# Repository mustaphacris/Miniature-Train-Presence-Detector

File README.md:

# Description du détecteur de présence de train miniature

Le schéma électronique présenté permet de détecter la présence d’un train miniature sur une portion de voie alimentée en courant continu. Le principe repose sur la mesure du courant consommé par la locomotive ou par une résistance de détection placée sur les essieux du train. Lorsque le train est présent, un faible courant circule dans la voie, ce qui permet au circuit de le détecter et de générer un signal exploitable (par exemple pour commander un signal lumineux, une automatisation ou un système d’arrêt).

Le montage est composé de plusieurs blocs fonctionnels successifs :

## 1. Convertisseur courant/tension (U1A – LM358)

La présence du train provoque le passage d’un petit courant dans la voie. Ce courant circule à travers une résistance de shunt (R1), ce qui produit une tension proportionnelle.
L’amplificateur opérationnel U1A convertit cette variation de courant en une tension mesurable et l’amplifie.
→ Il transforme la présence de courant en un signal électrique exploitable.

## 2. Filtre passe–bande autour de 10 kHz (L1, C5, C6)

Pour éviter les fausses détections (bruits électriques, variations lentes), le signal passe dans un filtre passe-bande centré sur 10 kHz.
Ce filtre ne laisse passer que les variations rapides voulues, ce qui améliore la précision de détection.

## 3. Amplificateur non-inverseur (U1B – LM358)

Le signal filtré est ensuite amplifié à un niveau suffisant.
→ Cela garantit que le signal soit suffisamment fort pour être traité dans l’étape suivante.

## 4. Détecteur de crête (D2, R9, C9)

Ce circuit rectifie le signal et conserve sa valeur maximale dans le condensateur C9.
→ Le signal alternatif devient une tension continue, représentative de la présence du train.

## 5. Comparateur (U3 – LM393)

Le comparateur compare cette tension détectée à une tension de référence fixée par un potentiomètre.

Si la tension dépasse le seuil → présence du train détectée

Si elle est en dessous → aucun train sur la voie

La sortie du comparateur peut ensuite activer une LED, un relais ou envoyer un signal vers un système de commande.

##  6. Alimentation

Le montage fonctionne avec +5V et -5V.
Le -5V est généré automatiquement par un convertisseur DC-DC à pompe de charge (MAX1044).
→ Cela permet l’utilisation correcte des amplificateurs opérationnels.

# Description du routage de la carte électronique

Le routage de la carte électronique a été réalisé sur deux couches de cuivre : la couche F.Cu (face avant) et la couche B.Cu (face arrière). Cela permet d’optimiser le passage des pistes, de réduire les interconnexions et d’obtenir une implantation compacte.

## 1. Routage sur la couche F.Cu (Face Avant)

L’image de la couche F.Cu montre principalement les pistes situées sur la face supérieure de la carte.
Sur cette face, on retrouve :

Les liaisons les plus courtes entre les composants sensibles, afin de réduire le bruit et les perturbations.

La majorité des connexions associées aux signaux analogiques, notamment celles liées aux amplificateurs opérationnels et aux étages de détection.

Le placement stratégique des condensateurs de découplage près des circuits intégrés pour une meilleure stabilité de l’alimentation.

Cette organisation permet de garantir une transmission du signal propre et stable.

## 2. Routage sur la couche B.Cu (Face Arrière)

La couche B.Cu représente le routage sur la face inférieure.
Cette couche est principalement utilisée pour :

Les retours à la masse (GND), permettant de créer un plan de masse continu.

Certaines pistes d’alimentation +5V et −5V provenant du convertisseur DC-DC.

Le passage de pistes complémentaires lorsque la face avant ne permet pas à elle seule les interconnexions.

L’utilisation des deux couches facilite une séparation claire entre signaux sensibles et alimentation, ce qui améliore les performances globales du circuit.

## 3. Visualisation 3D de la carte électronique

La troisième image représente la vue 3D de la carte électronique.
Cette modélisation permet :

De visualiser l’implantation réelle des composants (résistances, condensateurs, circuits intégrés, connecteurs, etc.),

De vérifier les dimensions et l’encombrement physique de la carte,

De s’assurer qu’aucune collision ou superposition de composants n’existe,

De préparer plus facilement l’assemblage et la fabrication.

La vue 3D constitue une étape essentielle avant l’envoi en fabrication, car elle permet une validation visuelle complète du design.

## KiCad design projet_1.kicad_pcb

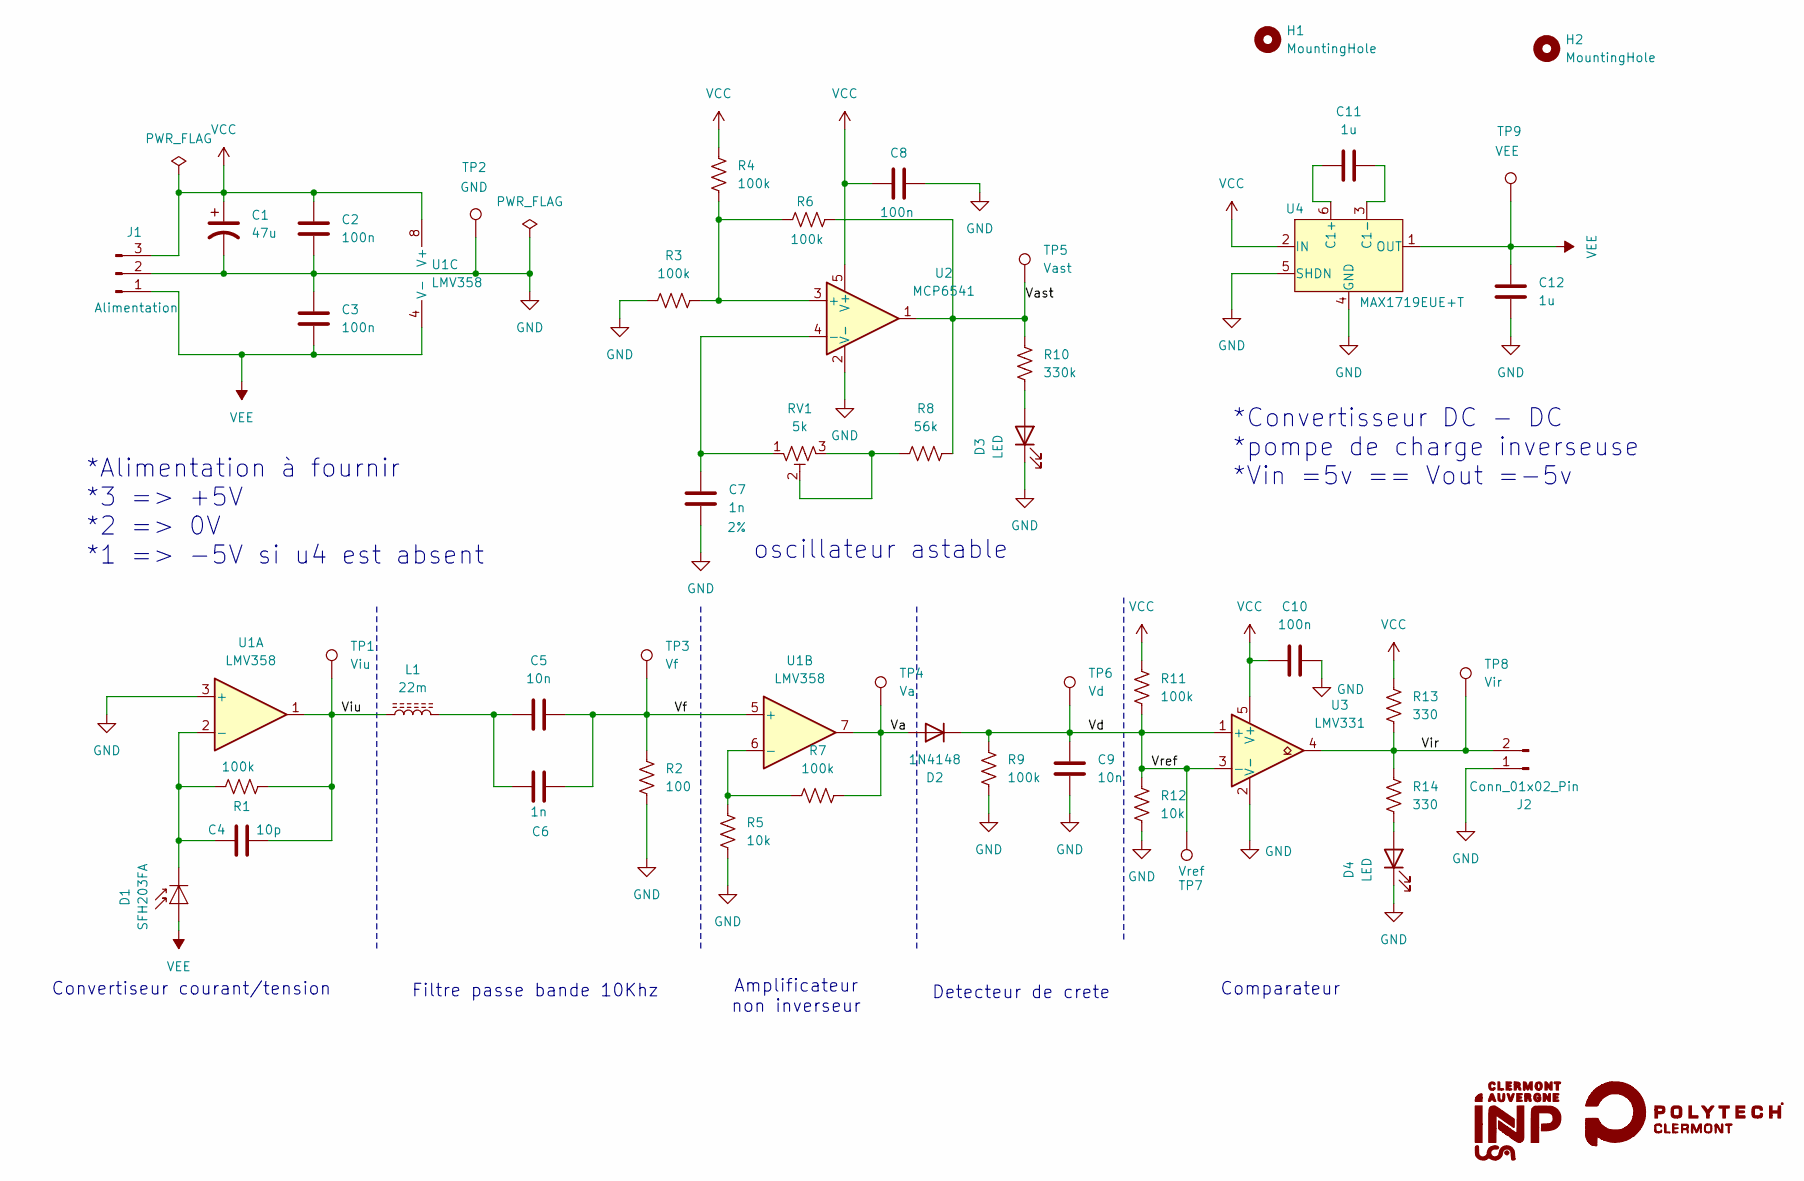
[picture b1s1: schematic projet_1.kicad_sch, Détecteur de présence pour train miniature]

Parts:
C1: 47u; CP_Elec_5x5.4
C2, C3, C8, C10: 100n; C_0805_2012Metric_Pad1.18x1.45mm_HandSolder
C4: 10p; C_0805_2012Metric_Pad1.18x1.45mm_HandSolder
C5, C9: 10n; C_0805_2012Metric_Pad1.18x1.45mm_HandSolder
C6: 1n; C_0805_2012Metric_Pad1.18x1.45mm_HandSolder
C7: 1n; C_0805_2012Metric_Pad1.18x1.45mm_HandSolder; Tolerance 2%
C11, C12: 1u; C_0805_2012Metric_Pad1.18x1.45mm_HandSolder
D1: SFH203FA; PinSocket_1x02_P2.54mm_Vertical
D2: 1N4148; D_DO-35_SOD27_P2.54mm_Vertical_AnodeUp
D3: LED; PinSocket_1x02_P2.54mm_Vertical
D4: LED; LED_0805_2012Metric_Pad1.15x1.40mm_HandSolder
H1, H2: MountingHole; MountingHole_3mm
J1: Alimentation; PinHeader_1x03_P2.54mm_Vertical
J2: Conn_01x02_Pin; PinHeader_1x02_P2.54mm_Vertical
L1: 22m; L_Radial_D8.7mm_P5.00mm_Fastron_07HCP
R1, R3, R4, R6, R7, R9, R11: 100k; R_0805_2012Metric_Pad1.20x1.40mm_HandSolder
R2: 100; R_0805_2012Metric_Pad1.20x1.40mm_HandSolder
R5, R12: 10k; R_0805_2012Metric_Pad1.20x1.40mm_HandSolder
R8: 56k; R_0805_2012Metric_Pad1.20x1.40mm_HandSolder
R10: 330k; R_0805_2012Metric_Pad1.20x1.40mm_HandSolder
R13, R14: 330; R_0805_2012Metric_Pad1.20x1.40mm_HandSolder
RV1: 5k; TRIM_TC33X-2-203E
TP1: Viu; TestPoint_Test-12
TP2: GND; TestPoint_Test-12
TP3: Vf; TestPoint_Test-12
TP4: Va; TestPoint_Test-12
TP5: Vast; TestPoint_Test-12
TP6: Vd; TestPoint_Test-12
TP7: Vref; TestPoint_Test-12
TP8: Vir; TestPoint_Test-12
TP9: VEE; TestPoint_Test-12
U1: LMV358; SOIC127P599X175-8N
U2: MCP6541; SOT95P280X145-5N
U3: LMV331; SOT-23-5_HandSoldering
U4: MAX1719EUE+T; SOT-23-6_Handsoldering

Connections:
/Va: D2.2 (A), R7.2, TP4.1, U1.7
/Vast: R6.2, R8.2, R10.1, TP5.1, U2.1
/Vd: C9.1, D2.1 (K), R9.1, R11.2, R12.1, TP6.1, TP7.1, U3.1 (+), U3.3 (-)
/Vf: C5.2, C6.2, R2.1, TP3.1, U1.5 (+)
/Vir: J2.2, R13.2, R14.1, TP8.1, U3.4
/Viu: C4.2, L1.1, R1.2, TP1.1, U1.1
GND: C1.2, C2.2, C3.1, C7.2, C8.2, C9.2, C10.2, C12.2, D3.1 (K), D4.1 (K), J1.2, J2.1, R2.2, R3.1, R5.2, R9.2, R12.2, TP2.1, U1.3 (+), U2.2 (V-), U3.2 (V-), U4.4 (GND), U4.5 (SHDN)
unnamed: C5.1, C6.1, L1.2
unnamed: C4.1, D1.1 (K), R1.1, U1.2 (-)
unnamed: D3.2 (A), R10.2
unnamed: D4.2 (A), R14.2
unnamed: R8.1, RV1.2, RV1.3
unnamed: R5.1, R7.1, U1.6 (-)
unnamed: R3.2, R4.2, R6.1, U2.3 (+)
unnamed: C7.1, RV1.1, U2.4 (-)
unnamed: C11.1, U4.6 (C1+)
unnamed: C11.2, U4.3 (C1-)
VCC: C1.1, C2.1, C8.1, C10.1, J1.3, R4.1, R11.1, R13.1, U1.8 (V+), U2.5 (V+), U3.5 (V+), U4.2 (IN)
VEE: C3.2, C12.1, D1.2 (A), J1.1, TP9.1, U1.4 (V-), U4.1 (OUT)

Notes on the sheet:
Convertiseur courant/tension
*Alimentation à fournir *3 => +5V *2 => 0V *1 => -5V si u4 est absent
Detecteur de crete
Amplificateur non inverseur
*Convertisseur DC - DC *pompe de charge inverseuse *Vin =5v == Vout =-5v
oscillateur astable
Comparateur
Filtre passe bande 10Khz

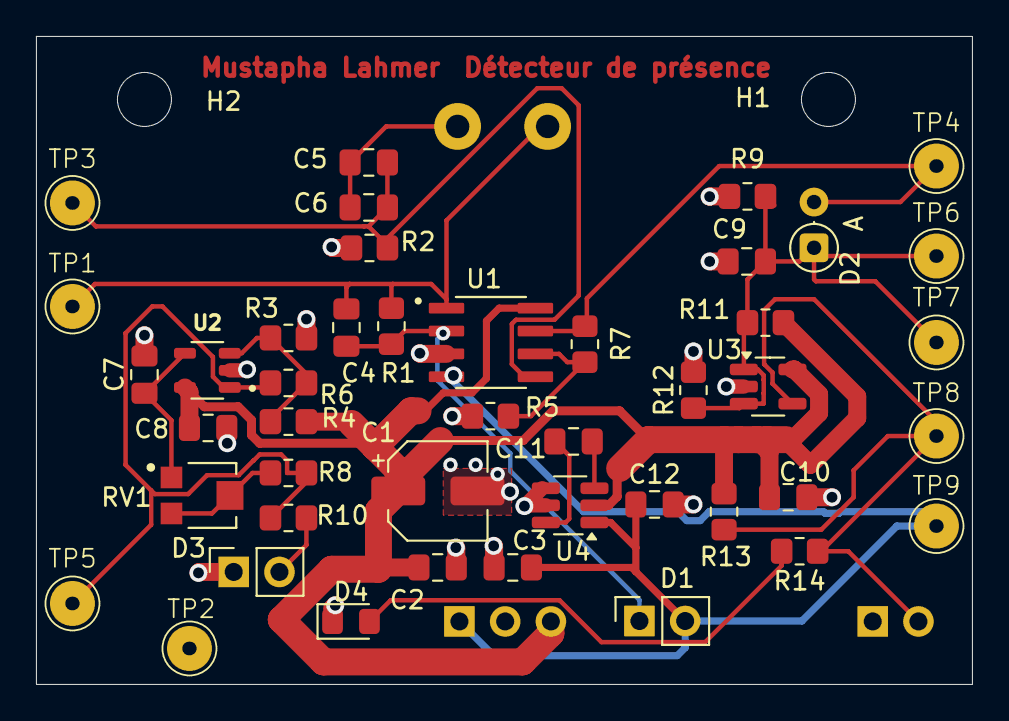
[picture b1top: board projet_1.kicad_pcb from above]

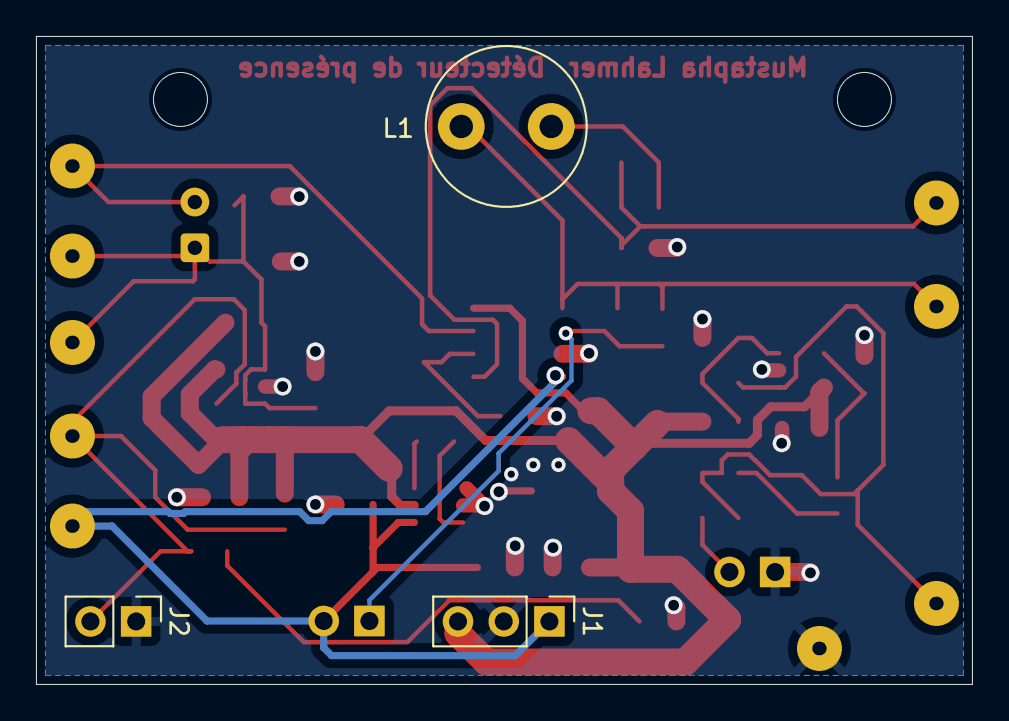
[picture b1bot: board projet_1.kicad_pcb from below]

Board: 2 copper layers, 52.0 x 36.0 mm, 49 parts (3 on the bottom side), 19 nets.
